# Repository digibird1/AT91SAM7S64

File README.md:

Things related to the AT91SAM7S64

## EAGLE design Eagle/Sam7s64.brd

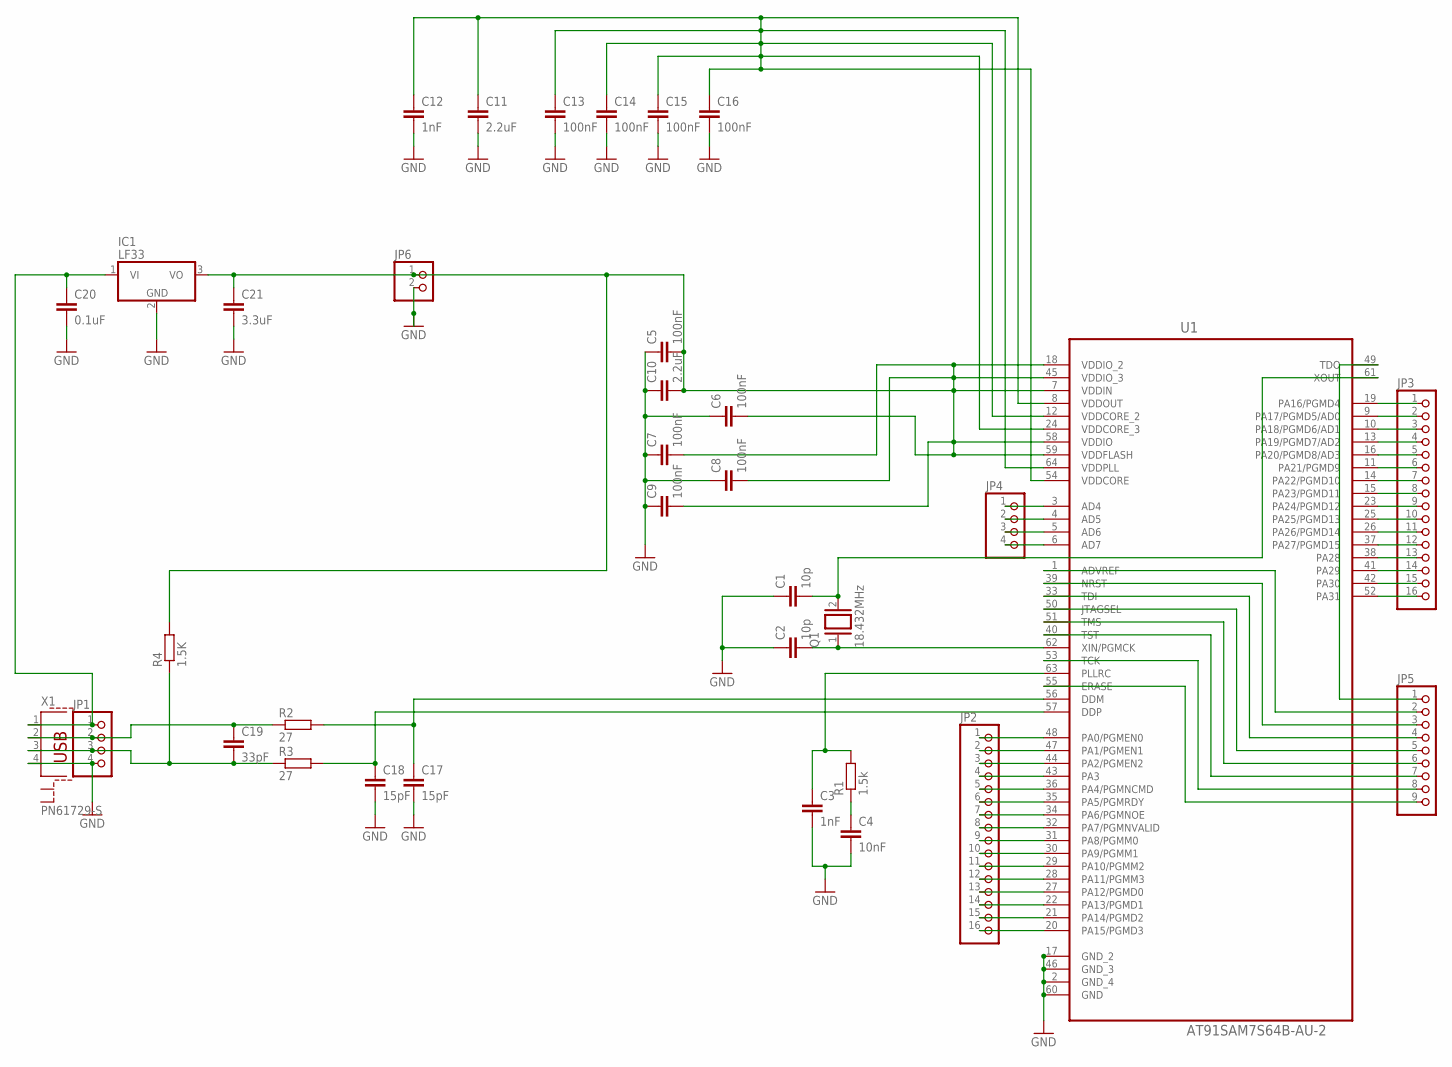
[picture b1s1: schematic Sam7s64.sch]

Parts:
C1, C2: 10p; C5B2.5
C3, C12: 1nF; C5B2.5
C4: 10nF; C5B2.5
C5, C6, C7, C8, C9, C13, C14, C15, C16: 100nF; C5B2.5
C10, C11: 2.2uF; C2.5-2
C17, C18: 15pF; C5B2.5
C19: 33pF; C5B2.5
C20: 0.1uF; C2.5-2
C21: 3.3uF; C2.5-2
IC1: LF33; TO220V
JP1, JP4: PINHD-1X4; 1X04
JP2, JP3: PINHD-1X16; 1X16
JP5: PINHD-1X9; 1X09
JP6: PINHD-1X2; 1X02
Q1: 18.432MHz; QS
R1: 1.5k; 0207/10
R2, R3: 27; 0207/10
R4: 1.5K; 0207/10
U1: AT91SAM7S64B-AU-2; QFP50P1200X1200X160-64N
X1: PN61729-S

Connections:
GND: C1.1, C2.1, C3.2, C4.2, C5.1, C6.1, C7.1, C8.1, C9.1, C10.1, C11.2, C12.2, C13.2, C14.2, C15.2, C16.2, C17.2, C18.2, C20.2, C21.2, IC1.2 (GND), JP1.4, JP6.2, U1.2 (GND_4), U1.17 (GND_2), U1.46 (GND_3), U1.60 (GND), X1.4
unnamed: C1.2, Q1.2, U1.61 (XOUT)
unnamed: C2.2, Q1.1, U1.62 (XIN/PGMCK)
unnamed: C17.1, R2.2, U1.56 (DDM)
unnamed: C3.1, R1.2, U1.63 (PLLRC)
unnamed: C5.2, C6.2, C7.2, C8.2, C9.2, C10.2, C21.1, IC1.3 (VO), JP6.1, R4.2, U1.7 (VDDIN), U1.18 (VDDIO_2), U1.45 (VDDIO_3), U1.58 (VDDIO), U1.59 (VDDFLASH)
unnamed: C4.1, R1.1
unnamed: C18.1, R3.2, U1.57 (DDP)
unnamed: C19.1, JP1.2, R2.1, X1.2
unnamed: C19.2, JP1.3, R3.1, R4.1, X1.3
unnamed: C20.1, IC1.1 (VI), JP1.1, X1.1
unnamed: C11.1, C12.1, C13.1, C14.1, C15.1, C16.1, U1.8 (VDDOUT), U1.12 (VDDCORE_2), U1.24 (VDDCORE_3), U1.54 (VDDCORE), U1.64 (VDDPLL)
unnamed: JP4.1, U1.3 (AD4)
unnamed: JP4.2, U1.4 (AD5)
unnamed: JP4.3, U1.5 (AD6)
unnamed: JP4.4, U1.6 (AD7)
unnamed: JP2.1, U1.48 (PA0/PGMEN0)
unnamed: JP2.2, U1.47 (PA1/PGMEN1)
unnamed: JP2.3, U1.44 (PA2/PGMEN2)
unnamed: JP2.4, U1.43 (PA3)
unnamed: JP2.5, U1.36 (PA4/PGMNCMD)
unnamed: JP2.6, U1.35 (PA5/PGMRDY)
unnamed: JP2.7, U1.34 (PA6/PGMNOE)
unnamed: JP2.8, U1.32 (PA7/PGMNVALID)
unnamed: JP2.9, U1.31 (PA8/PGMM0)
unnamed: JP2.10, U1.30 (PA9/PGMM1)
unnamed: JP2.11, U1.29 (PA10/PGMM2)
unnamed: JP2.12, U1.28 (PA11/PGMM3)
unnamed: JP2.13, U1.27 (PA12/PGMD0)
unnamed: JP2.14, U1.22 (PA13/PGMD1)
unnamed: JP2.15, U1.21 (PA14/PGMD2)
unnamed: JP2.16, U1.20 (PA15/PGMD3)
unnamed: JP3.1, U1.19 (PA16/PGMD4)
unnamed: JP3.2, U1.9 (PA17/PGMD5/AD0)
unnamed: JP3.3, U1.10 (PA18/PGMD6/AD1)
unnamed: JP3.4, U1.13 (PA19/PGMD7/AD2)
unnamed: JP3.5, U1.16 (PA20/PGMD8/AD3)
unnamed: JP3.6, U1.11 (PA21/PGMD9)
unnamed: JP3.7, U1.14 (PA22/PGMD10)
unnamed: JP3.8, U1.15 (PA23/PGMD11)
unnamed: JP3.9, U1.23 (PA24/PGMD12)
unnamed: JP5.2, U1.1 (ADVREF)
unnamed: JP5.3, U1.39 (NRST)
unnamed: JP5.4, U1.33 (TDI)
unnamed: JP5.5, U1.50 (JTAGSEL)
unnamed: JP5.6, U1.51 (TMS)
unnamed: JP5.7, U1.40 (TST)
unnamed: JP5.8, U1.53 (TCK)
unnamed: JP5.9, U1.55 (ERASE)
unnamed: JP5.1, U1.49 (TDO)
unnamed: JP3.10, U1.25 (PA25/PGMD13)
unnamed: JP3.11, U1.26 (PA26/PGMD14)
unnamed: JP3.12, U1.37 (PA27/PGMD15)
unnamed: JP3.13, U1.38 (PA28)
unnamed: JP3.14, U1.41 (PA29)
unnamed: JP3.15, U1.42 (PA30)
unnamed: JP3.16, U1.52 (PA31)

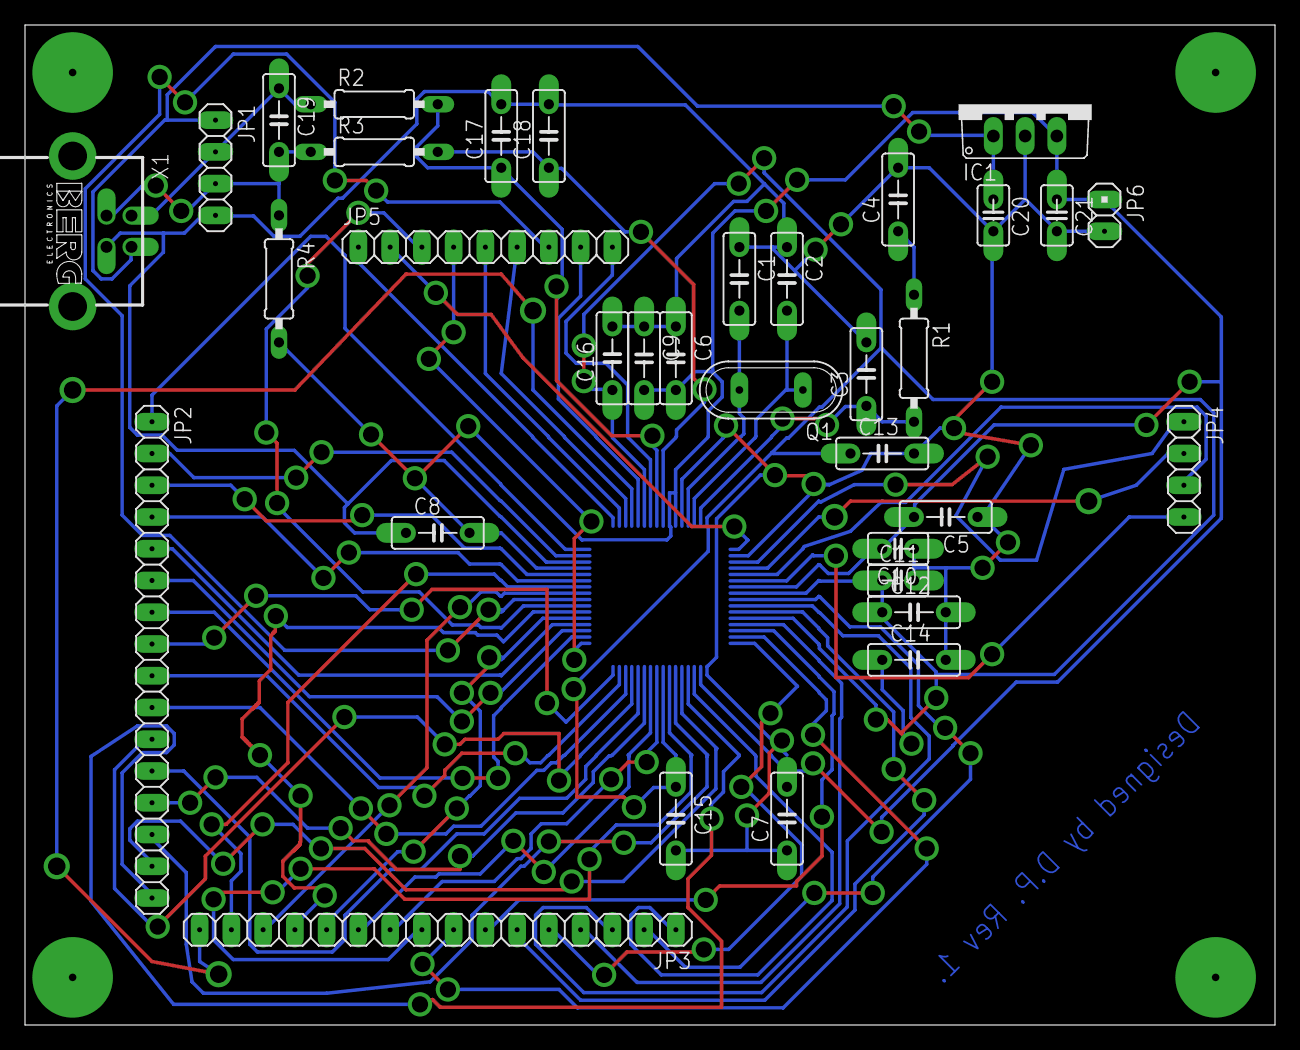
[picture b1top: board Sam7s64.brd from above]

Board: 2 copper layers, 100.0 x 80.0 mm, 35 parts (1 on the bottom side), 57 nets.

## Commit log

2014-04-16 Add drawing and sample prog
